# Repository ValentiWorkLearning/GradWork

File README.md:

# GradWork

Development board for smart-handwatch based on NRF52832 E73 module with C++20/CMake/VSCode based development flow

* Uses the C++20 features as wide as possible
* Uses С++20 coroutines for non-blocking interactions
* Port of LVGL 8.0 library for ST7789V/GC9A01 display and NRFSDK
* Simulator for fimware development without target MCU
* CI for Windows Simulator build and GCC build for target

### Article:
[C++20 Coroutines on NRF52832 with GTest](https://habr.com/ru/post/566070/)

### Revision v1.2

### Revision v1.0

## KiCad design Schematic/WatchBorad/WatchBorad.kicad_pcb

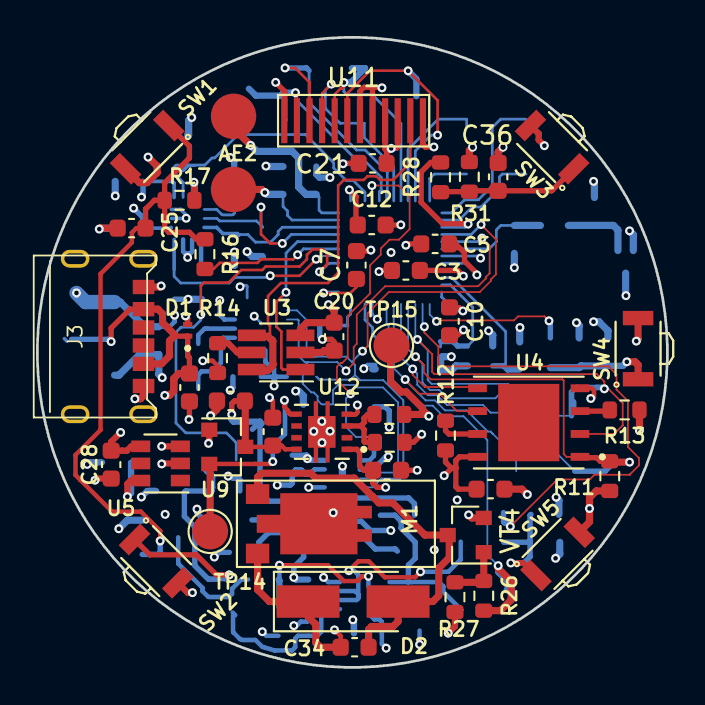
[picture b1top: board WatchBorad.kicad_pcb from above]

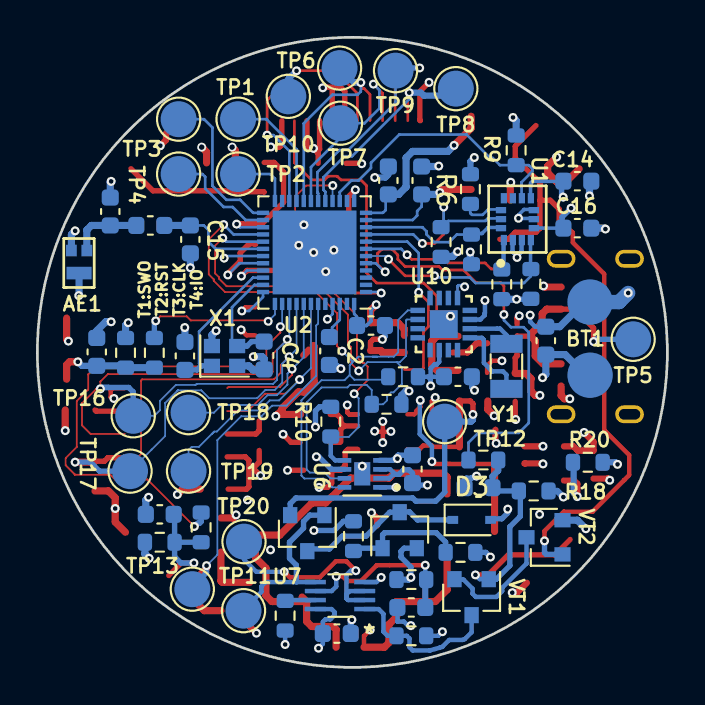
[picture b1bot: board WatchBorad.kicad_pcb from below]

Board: 4 copper layers, 35.0 x 35.0 mm, 119 parts (72 on the bottom side), 68 nets.

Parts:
3.9nH1: L; C_0603_1608Metric
AE1: Antenna_Chip; ANT2012LL13R2400A
AE2: Antenna_Loop; BatteryPads
BT1: Battery_Cell; BatteryPads
C1, C4: 10 pF; C_0603_1608Metric
C2, C8, C9, C20, C21, C23, C24, C28, C33, C40: 10 uF; C_0603_1608Metric
C3, C5: 100 pF; C_0603_1608Metric
C6, C7, C10, C12, C14, C16, C22, C25, C26, C27, C29, C32, C36, C37, C38: 100 nF; C_0603_1608Metric
C13, C15: 0.8 pF; C_0603_1608Metric
C18, C19: 130 pF; C_0603_1608Metric
C34: 100n X7R 16V; C_0603_1608Metric
D1: D_TVS; TVS_DFN1006
D2: 1A 20V; D_SMA_Handsoldering
D3: D; D_SOD-323
J3: TYPE-C-31-M-17
M1: Motor_DC; VibrationMorot4x4x11
R1, R2, R4, R5, R6, R7, R8, R9, R10, R11, R12, R13, R14, R17, R18, R20, R21, R22, R25, R27, R31, R32, R33: 10k; R_0603_1608Metric
R3: 330k; R_0603_1608Metric
R15, R16, R26, R28, R29, R30: 330; R_0603_1608Metric
R19: 220k; R_0603_1608Metric
R24: 1K; R_0603_1608Metric
R34: 10K; R_0603_1608Metric
SW1, SW2, SW3, SW4, SW5: SW_Push; SW_B3U-3000P
TP1, TP2, TP3, TP4, TP5, TP6, TP7, TP8, TP9, TP10, TP11, TP12, TP13, TP14, TP15, TP16, TP17, TP18, TP19, TP20: TestPoint; TestPoint_Pad_D2.0mm
U1: LSM6DSRTR; LSM6DSRTR_LGA-14L
U2: nRF52832-QFxx; QFN-48-1EP_6x6mm_Pitch0.4mm
U3: CAT4002ATD-GT3; SOT-23-6_Handsoldering
U4: MX25R1635F; W25Q128JVPIQ
U5: ME4055A; SOT-23-6
U6: MAX17048G+T10; MAX17048G
U7: SN74LVC2G74-EP_DCU_8; SN74LVC2G74
U9: MAX809S; SOT-23
U10: M41T62Q6F; QFN50P300X300X100-17N
U11: GC9A01; GC9A01_Extended_FPC
U12: TPS73501DRBR
VT1, VT2, VT4: SL2300; SOT-23
VT3, VT5: HX2301A; SOT-23
X1: Crystal_GND24_Small; Crystal_SMD_2016-4pin_2.0x1.6mm
Y1: Crystal_Small; Crystal_SMD_3215-2Pin_3.2x1.5mm

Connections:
+3V3: C9.1, C10.1, C12.1, C14.1, C16.1, C20.1, C21.1, C22.1, C34.1, C40.1, D2.1, M1.1, R3.1, R4.1, R5.1, R6.1, R7.1, R8.1, R9.1, R10.1, R11.1, R12.1, R13.1, SW3.2, SW4.2, SW5.2, TP15.1, U1.2, U1.3, U1.5, U1.8, U2.13, U2.36, U2.48, U3.3, U4.8, U11.3, U11.4, U12.1
+5V: C24.1, C28.1, D1.1, D3.2, J3.A9, J3.B9, R24.2, TP5.1, U5.4
+BATT: BT1.1, C6.1, C23.1, C27.1, C29.1, R1.1, R2.1, R21.2, R22.1, R25.1, SW1.2, SW2.2, U5.3, U6.2, U6.3, U7.8, U10.14, VT3.2
/DCDC&PB/DCDC_ENABLE: TP14.1, U9.2, U12.5
/DCDC&PB/DCDC_VIN: C32.1, C33.1, TP12.1, U9.3, U12.8, VT5.2
/DCDC&PB/Enable_motor: R26.2, TP13.1, U2.43
/DCDC&PB/LDO_RDIV: R3.2, R19.1, U12.3
/MCU/Backlight_EN_DIM: U2.8, U3.1
/MCU/DEC1: C7.1, U2.1
/MCU/DEC2: C5.1, U2.32
/MCU/DEC3: C3.1, U2.33
/MCU/DEC4: C2.1, U2.46
/MCU/DISP_CS: TP6.1, U2.20, U11.8
/MCU/DISP_DC: TP10.1, U2.22, U11.7
/MCU/DISP_RESET: TP8.1, U2.17, U11.11
/MCU/DISP_SCLK: TP7.1, U2.19, U11.9
/MCU/DISP_SDA: TP9.1, U2.18, U11.10
/MCU/FG_OD_ALRT_N: R10.2, U2.16, U6.5
/MCU/FLASH_CS: R11.2, TP17.1, U2.40, U4.1
/MCU/FLASH_MISO: TP16.1, U2.39, U4.2
/MCU/FLASH_MOSI: TP18.1, U2.41, U4.5
/MCU/FLASH_SCK: TP19.1, U2.42, U4.6
/MCU/I2C_SCL: R5.2, U1.13, U2.9
/MCU/I2C_SDA: R4.2, U1.14, U2.10
/MCU/LEDK: U3.4, U3.6, U11.2
/MCU/MPU_INT_1: R8.2, U1.4, U2.6
/MCU/MPU_INT_2: R9.2, U1.9, U2.15
/MCU/NC_PU: R6.2, U1.12
/MCU/NFC1: AE2.1, C19.1, U2.11
/MCU/NFC2: AE2.2, C18.1, U2.12
/MCU/PB_1_MCU: R15.2, U2.5
/MCU/PB_2_MCU: R16.2, U2.7
/MCU/PB_3_MCU: R28.2, U2.27
/MCU/PB_4_MCU: R29.2, U2.37
/MCU/PB_5_MCU: R30.2, U2.38
/MCU/SCL_FG: R1.2, U2.29, U6.7, U10.10
/MCU/SDA_FG: R2.2, U2.28, U6.8, U10.9
/MCU/SWD_RESET: TP2.1, U2.24
/MCU/SWD_SWDCLK: TP3.1, U2.25
/MCU/SWD_SWDIO: TP4.1, U2.26
/MCU/SWD_SWO: TP1.1, U2.21
/MCU/XC1: C1.1, U2.34, X1.1
/MCU/XC2: C4.1, U2.35, X1.3
/PSU_logic/PWR_SW_EN_N: TP11.1, U7.5, VT5.1
/PSU_logic/XI_RTC: U10.1, Y1.2
/PSU_logic/XO_RTC: U10.2, Y1.1
GND: AE1.2, BT1.2, C1.2, C2.2, C3.2, C4.2, C5.2, C6.2, C7.2, C8.2, C9.2, C10.2, C12.2, C13.2, C14.2, C15.2, C16.2, C18.2, C19.2, C20.2, C21.2, C22.2, C23.2, C24.2, C25.2, C26.2, C27.2, C28.2, C29.2, C32.2, C33.2, C36.2, C37.2, C38.2, C40.2, D1.2, J3.1, J3.A12, J3.B12, M1.CASE, R14.2, R17.1, R18.1, R19.2, R20.2, R27.2, R31.2, R32.2, R33.2, R34.2, U1.6, U1.7, U2.31, U2.45, U2.49, U3.2, U4.4, U5.2, U6.1, U6.4, U6.6, U6.9, U7.4, U9.1, U10.3, U10.5, U10.17, U11.1, U11.5, U11.6, U11.12, U12.4, U12.9, VT2.2, VT4.2, X1.2, X1.4
unnamed: 3.9nH1.1, AE1.1, C13.1
unnamed: 3.9nH1.2, C15.1, U2.30
unnamed: C8.1, R21.1, U7.6
unnamed: C25.1, R16.1, R17.2, SW1.1, VT2.1
unnamed: C26.1, R15.1, R18.2, SW2.1, VT1.1
unnamed: C34.2, D2.2, M1.2, VT4.3
unnamed: C36.1, R28.1, R31.1, SW3.1
unnamed: C37.1, R29.1, R32.1, SW4.1
unnamed: C38.1, R30.1, R33.1, SW5.1
unnamed: D3.1, VT3.3, VT5.3
unnamed: R7.2, U1.1
unnamed: R12.2, U4.7
unnamed: R13.2, U4.3
unnamed: R14.1, U3.5
unnamed: R20.1, U5.6
unnamed: R22.2, U7.1, VT1.3
unnamed: R24.1, R34.1, VT3.1
unnamed: R25.2, U7.7
unnamed: R26.1, R27.1, VT4.1
unnamed: TP20.1, U7.2, U7.3
unnamed: VT1.2, VT2.3

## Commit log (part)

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2021-01-06 Moved SDL dependency to Conan package manager (#20)
    * Local draft for mocked SPI [SPI][CORO]
    * Removed SDL package from lv_drives dependency [PACKAGE]
    * Added SDL package with Conan [PACKAGE]
    * Updated CI for supporting Conan [PACKAGE]
    * CI fix[PACKAGE]
    * CI fix[PACKAGE]
2021-01-06 Removed unnecessary log from buttton tests [BUTTONS][LOG]
2021-01-07 Added more initialization commands to cppcoro_thought [CORO]
2021-01-08 Added Event for display initialization [CORO]
2021-01-16 Added CoroQueueMainLopp [CORO]
2021-01-18 Added draft of shortened initalize version [CORO]
2021-01-19 Fixed build,mistake in the include path
2021-01-19 Added compact display usage [CORO]
2021-01-19 Changed folder for GCC toolchain cache[CI]
2021-01-19 Attempted to fix build [CI]
2021-01-19 Added caching for ARM-GCC builds (#21)
    * Changed folder for GCC toolchain cache[CI]
    * Added caching to gcc build
    * Attempted to fix build [CI]
    * Attempted to check cache [CI]
2021-01-30 Added Clang workflow [CLANG]
2021-03-04 Fixed compilation issue for MSVC compiler [CORO]
2021-03-07 Draft project for debug purpouse [CORO]
2021-03-11 Toolchain update [TOOLCHAIN]
2021-03-19 Draft migration to LVGL v8.0
2021-03-20 Working draft of fill rectange [CORO]
2021-03-22 Added a few fixes for styles init, indev initialize & lifetime [LVGL]
2021-03-22 Fixed lv_config and increased heap size [LVGL]
2021-03-22 Fixed display init/fillBuff commands [CORO]
2021-03-22 Added compiler check disable[temporary]. Updated gtest package [CONAN]
2021-03-30 Added more noexcept to the codebase [OPTIMIZE]
2021-03-31 Removed copy parameter from widget's creation [LVGL]
2021-03-31 Updated fonts [LVGL]
2021-04-02 Fixed drawing crash [LVGL]
2021-04-03 Added FreeRTOS support
2021-04-03 Slightly corrected example [FreeRTOS]
2021-04-04 Removed submodule [FreeRTOS]
2021-04-04 Removed unncessary build deps [FreeRTOS]
2021-04-05 Added min examples for testing [CORO]
2021-04-13 Fixed Main Window Widgets appearance [LVGL8_0]
2021-04-13 Fixed health page appearance. Added new lv_conf.h [LVGL]
2021-04-19 Draft of restore-in-spi implementation [SPI][CORO]
2021-04-19 Fixed command-to-send size [SPI][CORO]
2021-04-20 Added extra logging fmtlib to coro-tuple [CORO]
2021-04-29 Fixed implementation for the display_coro_comact [CORO]
2021-04-30 Draft of tests for TemplatedSpi [CORO][SPI]
2021-05-02 Added obtaining for bus transactions to vector [SPI][TESTING]
2021-05-05 Slightly changed nrf backend c-tor[SPI][CORO]
2021-05-05 Just for testing fixed spi_wrapper_async[SPI][CORO]
2021-05-05 Fixed GPIO namespace include[GPIO]
2021-05-05 More noexcept to the codebase [NOEXCEPT]
2021-05-06 Fixed SPI Instance for display [SPI]
2021-05-21 Fixed Spi handle initialization [CORO][TEMPLATED]
2021-05-25 Fixed templated display driver [CORO]
2021-05-25 Launched ble stack [BLE]
2021-05-26 Moved coroutine queue processing forward [CORO]
2021-05-26 Added parallel jobs up to 8 [VSCODE]
2021-05-26 Added draft of Coroutine<Result> [CORO]
2021-05-26 Fixed warning [GUI]
2021-05-26 Fixed Default driver build ; [GC_DISPLAY]
2021-05-26 Dependencies update [3RD PARTY]
2021-05-26 LVGL fixed CMake lists [LVGL]
2021-05-29 Added clangformat file [CLANGFORMAT]
2021-06-01 Working draft on Sync Wait implementation [CORO]
2021-06-01 Implemented draft of Winbond coroutine driver [CORO]
2021-06-02 Implemented xfer transaction for SPI nordic backend [CORO]
2021-06-02 Fixed driver implementation [CORO]
2021-06-02 Jedec formatted to hex [CORO]
2021-06-03 Removed tecnical debt from gs_platform_layer(old display driver)[CORO]
2021-06-03 Get rid off old display driver implementation [CORO]
2021-06-03 Updated readme for C++20 features mention
2021-06-06 Added paragraphs 1-7 for coroutine description [CORO]
2021-06-06 Added paragraphs 7,8 [CORO]
2021-06-06 Added article examples to the coroutine-tests. Added wandbox link to the complete example [CORO][DOCS]
2021-06-07 Fun. Board led sequence blink [CORO]
2021-06-09 Implemented chip-select choose for the driver user [CORO]
2021-06-09 Added more SPI flash options [CORO]
2021-06-10 Fixed SPI implementation [CORO]
2021-06-10 Misstypes corrections [DOCS]
2021-06-11 Fixed SyncWait for void-return type [CORO]
2021-06-13 Code formatting common-display-coro[CORO]
2021-06-13 Added draft of SPI FLASH mocking suite [MOCK]
2021-06-14 Fixed test suite for SpiFlashDriver [FLASH]
2021-06-14 Added flash read test #17 [WINBOND]
2021-06-15 Fixed symmetric transfer instead of raw .resume() #17 [FLASH]
2021-06-15 Fixed magras proposal [DOCS]
2021-06-17 Fixed LCSC schematic link :Schematic [SCHEMATIC]
2021-06-18 Fixed extra spaces for MissedParts.md
2021-06-19 Fixed components references for 0603 resistors and capacitors[SCHEMATIC]
2021-06-19 Updated missed parts list.md
2021-06-19 Updated 0603 components from hand-solder version to fabrical
2021-06-20 Added more routings for components.Moved MCU to the top layer. Added 4-layer board setup
2021-06-20 Keepout fix for the antenna shape
2021-06-20 Updated parts list accroding to the Ruslan fixes
2021-06-20 Updated missing parts list
2021-06-20 Fixed Type-C position. Added 3Dmodel for winbond
2021-06-24 Added updated SyncWait example. Fixed main intro #26
2021-06-24 Added LICENSE
2021-06-24 Fixed typo #26
2021-06-29 Updated & fixed missed SCH parts list
2021-06-29 Fixed buttons layout. Added layout draft for the display testpoints [SCHEMATIC]
2021-07-03 Added missed footprints
2021-07-03 Grammarly fixed [DOCS]
2021-07-03 Fixed 3D models paths
2021-07-03 Fixed DRC warnings
2021-07-03 Fixed layout for display & SWD interface
2021-07-05 Small grammarly fixes [DOCS]
2021-07-05 Removed extra buildstep with bincrafters remote setup[BUILD]
2021-07-06 Added battery print
2021-07-06 Updated footprints to the actual one
2021-07-06 Added route for crystal
2021-07-06 Added route for SPI-FLASH
2021-07-06 Added routing for power plane
2021-07-07 Finished 3V3 routing
2021-07-07 Added display's GND via
2021-07-08 Added PCB route for GND vias
2021-08-23 Updated toolchain to GCC10.3 [TOOLCHAIN]
2021-09-22 Updated workflows file
2021-09-24 Updated falgs for building with coroutines in the GNU compiler
2021-10-12 Attempted to fixup CI build for Windows and Linux
2021-10-12 Introduced REDUCE_LVGL_BINARY_SIZE option for switching between LVGL with Os and without any optimizations
2021-10-14 CMake option REDUCE_LVGL_BINARY_SIZE should be available only under GNU builds
2021-10-14 After merge corrections
2021-10-14 Updated workflows file for the github actions. Removed conan libraries download step. Changed simulator build directory
2021-10-14 Added linux-desktop-configuration build
2021-10-14 Fixed syntax issues in build.yml
2021-10-14 Fixed indentation in build.yml
2021-10-14 sudo apt-get on linux
2021-10-14 Fixed build.yml windows build directory
2021-10-14 Renamed linux desktop to linux dekstop simulator CI
2021-10-15 Removed gtest from submodules
2021-10-15 Moved gtest to the conan packages
2021-10-17 Added pull-up resistors for I2C bus. Refactored PCB for the Front layer
2021-10-18 Added routing for the power supply. Fixed schematic issue with the charger
2021-10-19 Removed MAX30102 from schemtic and PCB
2021-10-19 Rerouted MPU_INT area [PCB]
2021-10-19 Completed draft PCB layout routing
2021-10-20 Added Kicad libraries as a submodule [SCHEMATIC]
2021-10-21 Attempted to fixup cmake build for visual studio [SIMULATOR]
2021-10-21 Revert "Removed default font from LVGL config"
    This reverts commit 4e84bbb35766a1f7b5d312761488f3d2e007ab43.
2021-10-23 Removed gerbers from repo
2021-10-24 Added schematic files annotations [SCHEMATIC]
2021-10-24 Added routing for the BLE ANTENNA [SCHEMATIC]
2021-10-25 Fixed PCB Layout for LDO vias [PCB]
2021-10-25 Replaced power traces with the polygons [PCB]
2021-10-25 Added NFC antenna pads on the PCB [NFC][PCB]
2021-10-26 Corrected polygon fills for the power layer
2021-10-26 Updated schematic components submodule [PCB]
2021-10-27 Removed cmake run action. Changed to a raw cmake call instead
2021-10-27 Removed FMTLIB headeronly build
2021-10-27 Fixed windows workflow
2021-10-27 Removed DRC markers [PCB]
2021-10-27 Fixed capacitors near the fuel gauge [PCB]
2021-10-27 Added testpoint to the on/off circuit [PCB][SCHEMATIC]
2021-10-27 Removed away the trace between Battery input and the battery charger [PCB]
2021-10-28 Added missed components to the symbol lists [SCHEMATIC]
2021-10-28 Updated kicad libaries root dependency [SCHEMATIC][PCB]
2021-10-28 Added missed resistors to the lcsc [SCHEMATIC][BOM]
2021-10-30 Added D-trigger instead of the MAX switching chip
2021-10-30 Fixed silkscreen appearance [PCB]
2021-10-31 After draft-plot corrections [PCB]
2021-11-03 Attempted to fix linux build. Moved LVGL fonts to a separate library
2021-11-03 Implemented #34 - replacement of the ASSERT_EQ macro in test
2021-11-03 Added fmt for logging faciliies
2021-11-03 Moved GTest to conan instead of building a submodule (#31)
    * Removed gtest from submodules
    * Moved gtest to the conan packages
    * Removed gtest from submodules
    * Moved gtest to the conan packages
    * Attempted to fixup cmake build for visual studio [SIMULATOR]
    * Attempted to fixup cmake build for visual studio [SIMULATOR]
2021-11-07 Attempted to force-building SDL2 package
2021-11-07 Removed unnecessary calls to the tick_thread since SDL does this internally
2021-11-07 Changed Power MUX circuit to the transistors
2021-11-07 Fixed D3 footpint [SCHEMATIC][PCB]
2021-11-08 Fixed crash under Windows platform [ASAN]
2021-11-08 Fixed ram overflow for ARM.[LVGL]
2021-11-09 Attempted to fixup LVGL crash with out of memory
2021-11-14 Fixed silkscreen on the bottom layer [PCB]
2021-11-16 Fixed a few board issues. Removed extra power plane from the Battery connetion #38
2021-11-17 Fixed accelerometer 3d model path [3D MODELS]
2021-11-19 Added draft of the littlefs system [FS] #17
2021-11-22 Draft wrapper over littlefs types
2021-11-22 Implemented draft of heap block device
2021-12-05 Working draft of the filesystem mounting
2021-12-08 Implemented working draft of FS driver and heap-block-device
2021-12-10 Impleemnted support of the small chunks reading [FILESYTEM]
2021-12-11 An attempt to add coroutines support to the FS driver [FILESYSTEM]
2021-12-30 Added SON-8 3D model
2021-12-31 Added antenna 3D Model to PCB [PCB]
2021-12-31 Updated README files
2022-01-18 Implemented littlefs MVP with coroutines support
2022-01-18 Switched to original coro-based littlefs submodule
2022-01-18 Fixed build on ARM with shadowed template parameter #17
2022-01-19 Added forgotten CMakeLists.txt file to the filesystem #17
2022-02-03 Fixed coroutine filesystem tests #17
2022-02-06 Added interface for spi-based block device wrapper #17
2022-03-22 Updated littlefs CMakeLists
2022-03-22 Updated conan-cmake version
2022-03-23 Application class has been changed to the singleton
2022-03-25 Application instance was moved to Singleton
2022-03-25 Success compilation of the coro-fs implementation on the ARM target
2022-03-25 Removed LOG_DEBUG_ENDL macro
2022-03-26 Fixed write-read data from the SPI-flash
2022-04-01 Added logging adaptor to spiblockdevice
2022-04-01 Extented logger service with the log level disabling
2022-04-01 Added filesystem init to the watchboard
2022-04-01 Changed dump of the display refresh time to the single log line
2022-04-01 Decreased severity and removed redundant logs
2022-04-02 Implemented colorful logging to the RTT logger backend
2022-05-29 [coroutine][filesystem]added coroutine loop executor for testing purouses
2022-08-15 [firmware][tests] added missed CMakeLists.txt for the testing_common target
2022-08-17 [firmware][filesystem] added lfs_util_desktop.h for the firmware simulator configuration
2022-11-19 [mac_m1]: added support for apple clang
2022-11-23 [mac_m1] replaced std::string to const char* for weekdays label
2023-03-27 [graphics] fixed automatic pages switch task
2023-03-27 [ci] updated conan-cmake version

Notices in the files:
parts and their libraries:
Copyright 2021 Accelerated Designs. All rights reserved.
